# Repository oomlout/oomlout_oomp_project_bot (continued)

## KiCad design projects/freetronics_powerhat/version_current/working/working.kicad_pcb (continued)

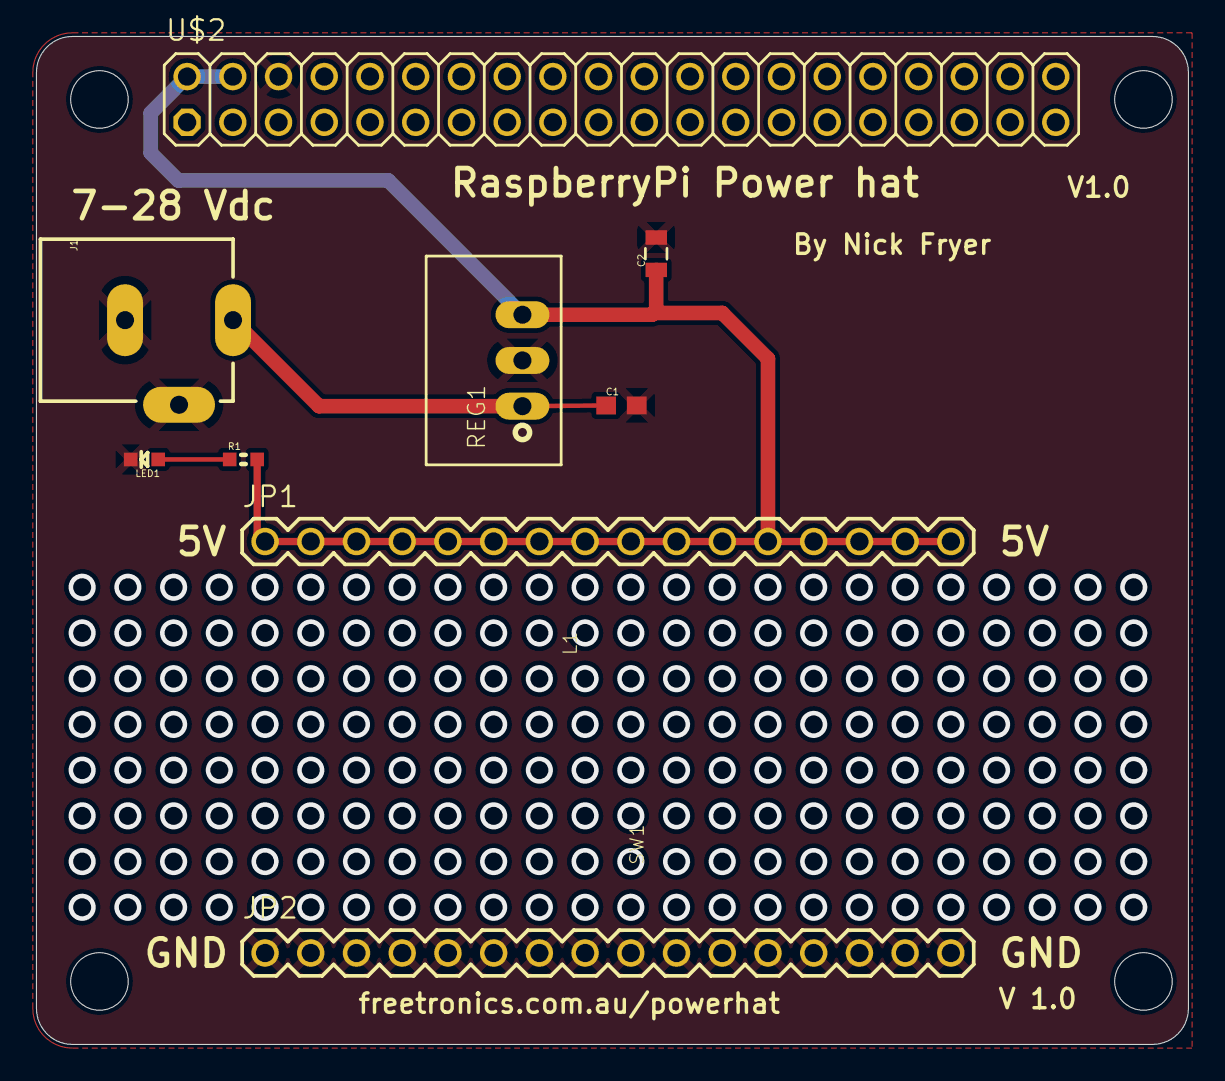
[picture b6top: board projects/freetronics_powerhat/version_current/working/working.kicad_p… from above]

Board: 2 copper layers, 64.0 x 56.0 mm, 13 parts (0 on the bottom side), 4 nets.

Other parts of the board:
@HOLE0, @HOLE1, @HOLE2, @HOLE3: (no value)

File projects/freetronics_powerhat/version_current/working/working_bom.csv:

"Id";"Designator";"Footprint";"Quantity";"Designation";"Supplier and ref";
1;"REG1";"K78XX-500R3";1;"K7805-500R3";;;
2;"JP2,JP1";"1X16";2;"M16PTH";;;
3;"@HOLE0,@HOLE2,@HOLE1,@HOLE3";"";4;"";;;
4;"J1";"POWER_JACK_PTH_SLOTS";1;"POWER_JACKPTH_SLOTS";;;
5;"C1";"0603";1;"1uF 0603";;;
6;"C2";"0805";1;"10uF";;;
7;"R1";"0603";1;"2.2k";;;
8;"U$2";"2X20";1;"M40PTH";;;
9;"LED1";"LED-0603";1;"Blue";;;

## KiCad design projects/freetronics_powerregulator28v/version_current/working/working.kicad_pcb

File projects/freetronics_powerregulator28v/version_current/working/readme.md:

# PowerRegulator28V by freetronics  
This is a harvested standardized copy of a project from github.  
The original project can be found at:  
https://github.com/freetronics/PowerRegulator28V  
Please consult that link for additional, details, files, and license information.  
Note: It was auto harvested and if the original repo had more than one board file or anything out of the ordinary the files here are likely not representative.

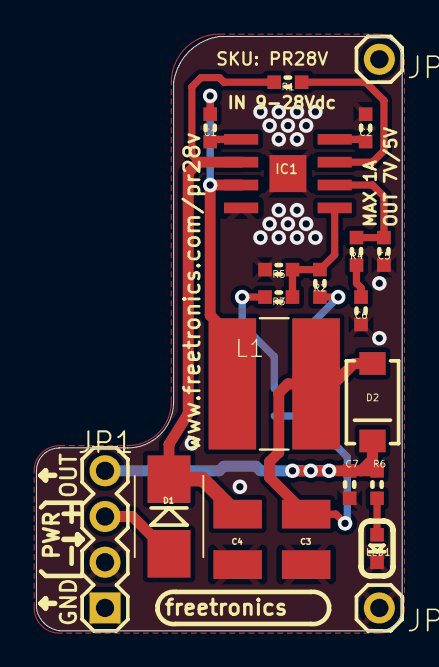
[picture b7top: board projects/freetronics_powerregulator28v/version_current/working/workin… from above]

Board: 2 copper layers, 20.3 x 33.0 mm, 22 parts (1 on the bottom side), 14 nets.

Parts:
C1: 10nF 50V; 0603
C2: 100nF; 0603
C3: 22uF 10V 1210 ceramic; C1210
C4: 10uF 50V 1210 ceramic; C1210
C5: 22pF NOT PLACED; 0603
C6: 2.2nF 0603; 0603
C7: 1uF 16V; 0603
D1: SS16 SCHOTTKY SMA; SMA-SMB-DIODE
D2: SK34A-LTP 3A 40V SCHOTTKY; SMA-DIODE
IC1: EUP3476SO08T; SO08T
JP1: Pwr Header; 1X04
JP2, JP3: 1X01
L1: CDRH6D38SMT; CDRH
LED1: BLUE; LED-0603
R1: 100K 0603; 0603
R2: 82.5K 1% 0603; 0603
R3: 187K 1% 0603; 0603
R4: 15K 0603; 0603
R5: 10K 1% 0603; 0603
R6: 1K; 0603
SJ1: 5VSEL; SJ

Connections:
GND: C2.1, C3.2, C4.2, C5.2, C6.2, C7.2, IC1.4, IC1.9, JP1.1, JP1.2, JP3.1, LED1.C, R5.1
unnamed: R3.1, SJ1.1
unnamed: IC1.7, R1.1
unnamed: IC1.5, R2.2, R3.2, R5.2
unnamed: C5.1, IC1.6, R4.2
unnamed: C6.1, R4.1
unnamed: C1.2, IC1.1
unnamed: C2.2, IC1.8
unnamed: C1.1, IC1.3, L1.1
unnamed: LED1.A, R6.2
POS: D1.A, JP1.3
VFEED: C3.1, D2.A, L1.2, R2.1, SJ1.2
VIN: C4.1, D1.C, IC1.2, R1.2
VOUT: C7.1, D2.C, JP1.4, R6.1

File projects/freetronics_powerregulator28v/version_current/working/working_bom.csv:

"Id";"Designator";"Footprint";"Quantity";"Designation";"Supplier and ref";
1;"C7";"0603";1;"1uF 16V";;;
2;"C5";"0603";1;"22pF NOT PLACED";;;
3;"LED1";"LED-0603";1;"BLUE";;;
4;"C3";"C1210";1;"22uF 10V 1210 ceramic";;;
5;"R4";"0603";1;"15K 0603";;;
6;"R6";"0603";1;"1K";;;
7;"D2";"SMA-DIODE";1;"SK34A-LTP 3A 40V SCHOTTKY";;;
8;"JP1";"1X04";1;"Pwr Header";;;
9;"C4";"C1210";1;"10uF 50V 1210 ceramic";;;
10;"JP2,JP3";"1X01";2;"";;;
11;"IC1";"SO08T";1;"EUP3476SO08T";;;
12;"R1";"0603";1;"100K 0603";;;
13;"R3";"0603";1;"187K 1% 0603";;;
14;"C6";"0603";1;"2.2nF 0603";;;
15;"D1";"SMA-SMB-DIODE";1;"SS16 SCHOTTKY SMA";;;
16;"C1";"0603";1;"10nF 50V";;;
17;"R2";"0603";1;"82.5K 1% 0603";;;
18;"R5";"0603";1;"10K 1% 0603";;;
19;"L1";"CDRH";1;"CDRH6D38SMT";;;
20;"C2";"0603";1;"100nF";;;
21;"SJ1";"SJ";1;"5VSEL";;;
